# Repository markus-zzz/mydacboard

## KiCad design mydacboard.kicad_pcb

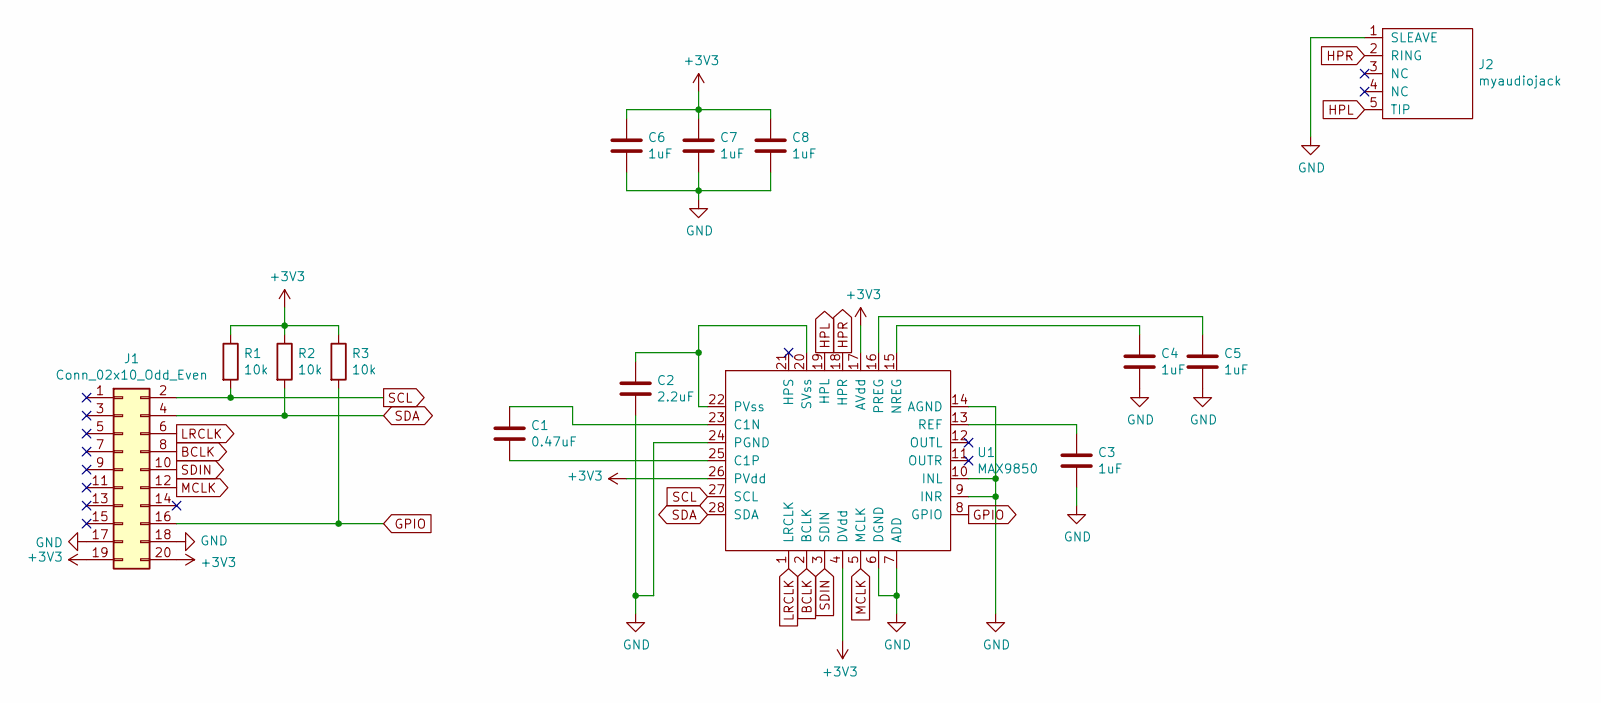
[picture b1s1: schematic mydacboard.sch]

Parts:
C1: 0.47uF; C_0603_1608Metric
C2: 2.2uF; C_0603_1608Metric
C3, C4, C5, C6, C7, C8: 1uF; C_0603_1608Metric
J1: Conn_02x10_Odd_Even; PinSocket_2x10_P2.54mm_Vertical
J2: myaudiojack
R1, R2, R3: 10k; R_0603_1608Metric
U1: MAX9850; TQFN-28-1EP_5x5mm_P0.5mm_EP3.25x3.25mm

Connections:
+3V3: C6.1, C7.1, C8.1, J1.19, J1.20, R1.1, R2.1, R3.1, U1.4 (DVdd), U1.17 (AVdd), U1.26 (PVdd)
BCLK: J1.8, U1.2 (BCLK)
GND: C2.2, C3.2, C4.2, C5.2, C6.2, C7.2, C8.2, J1.17, J1.18, J2.1 (SLEAVE), U1.6 (DGND), U1.7 (ADD), U1.9 (INR), U1.10 (INL), U1.14 (AGND), U1.24 (PGND)
GPIO: J1.16, R3.2, U1.8 (GPIO)
HPL: J2.5 (TIP), U1.19 (HPL)
HPR: J2.2 (RING), U1.18 (HPR)
LRCLK: J1.6, U1.1 (LRCLK)
MCLK: J1.12, U1.5 (MCLK)
unnamed: C1.1, U1.23 (C1N)
unnamed: C1.2, U1.25 (C1P)
unnamed: C2.1, U1.20 (SVss), U1.22 (PVss)
unnamed: C3.1, U1.13 (REF)
unnamed: C4.1, U1.15 (NREG)
unnamed: C5.1, U1.16 (PREG)
SCL: J1.2, R1.2, U1.27 (SCL)
SDA: J1.4, R2.2, U1.28 (SDA)
SDIN: J1.10, U1.3 (SDIN)

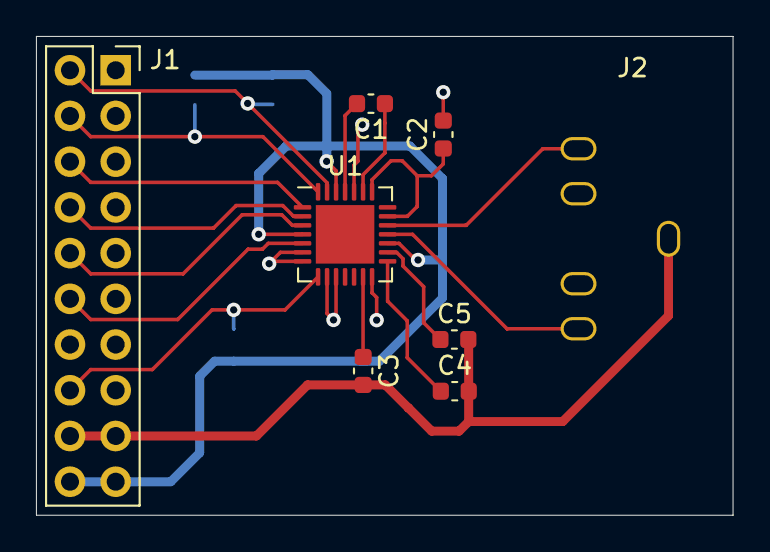
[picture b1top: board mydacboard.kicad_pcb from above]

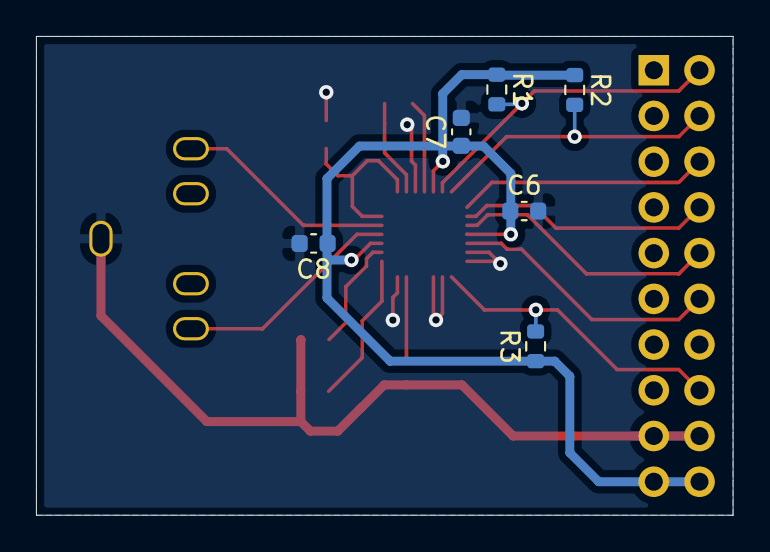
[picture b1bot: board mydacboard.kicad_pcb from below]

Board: 2 copper layers, 38.7 x 26.6 mm, 14 parts (6 on the bottom side), 17 nets.

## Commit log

2022-01-01 MAX9850 DAC expansion board - import
2022-01-01 Updated audiojack U->J ref
2022-01-03 Updated audio jack footprint
    Audio jack hole dimensions are now 1.65x0.95mm.
    Sent to aisler.net for manufacturing.
